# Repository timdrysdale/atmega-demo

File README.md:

# atmega-demo
PCB to demonstrate atmega microcontroller together with ACS712 and temperature sensor.

## Purpose

This board will be used to monitor power consumption and temperature in remote lab boxes.

## Schematic

The key components are an Atmega328P, a CH340 USB transceiver, an ACS712 current sensor and a simple analog temperature sensor. DTR reset is enabled to support re-programming over USB, while ICSP header is supplied for initial programming. Both CH340 and Atmega are using 12MHz crystals, which yields 0.1% baud rate error at 57600 baud for the Atmega.

## BOM

|Comment             |Designator         |Footprint                                                 |LCSC    |
|--------------------|-------------------|----------------------------------------------------------|--------|
|0.1n                |C1                 |Capacitor_SMD:C_0603_1608Metric                           |C100040 |
|100n                |C8,C11,C12         |Capacitor_SMD:C_0603_1608Metric                           |C14663  |
|0.1u                |C2,C3              |Capacitor_SMD:C_0603_1608Metric                           |C14663  |
|100n                |C4                 |Capacitor_SMD:C_0805_2012Metric                           |C49678  |
|22p                 |C5,C6              |Capacitor_SMD:C_0603_1608Metric                           |C1653   |
|4n7                 |C7                 |Capacitor_SMD:C_0603_1608Metric                           |C53987  |
|33p                 |C9,C10             |Capacitor_SMD:C_0603_1608Metric                           |C1663   |
|Green               |D1                 |LED_SMD:LED_0603_1608Metric                               |C72043  |
|Blue                |D2                 |LED_SMD:LED_0603_1608Metric                               |C72043  |
|PRTR5V0U2X          |D3                 |Package_TO_SOT_SMD:SOT-143                                |C2827688|
|Conn_01x04_Male     |J1                 |Connector_PinSocket_2.54mm:PinSocket_1x04_P2.54mm_Vertical|        |
|AVR_ICSP            |J2                 |Connector_PinHeader_2.54mm:PinHeader_2x03_P2.54mm_Vertical|        |
|USB_B_Micro         |J3                 |Connector_USB:USB_Micro-B_Amphenol_10118194_Horizontal    |C132563 |
|Screw_Terminal_01x02|J4                 |TerminalBlock:TerminalBlock_bornier-2_P5.08mm             |        |
|10u                 |L1                 |Inductor_SMD:L_0805_2012Metric                            |C1046   |
|10K                 |R1                 |Resistor_SMD:R_0603_1608Metric                            |C25804  |
|68                  |R2,R3              |Resistor_SMD:R_0603_1608Metric                            |C27592  |
|1M                  |R4                 |Resistor_SMD:R_0603_1608Metric                            |C22935  |
|NO                  |SW1                |Button_Switch_SMD:SW_SPST_PTS810                          |C116501 |
|TestPoint           |TP1,TP2,TP3,TP4,TP5|TestPoint:TestPoint_Keystone_5015_Micro-Minature          |C238130 |
|ACS712xLCTR-20A     |U1                 |Package_SO:SOIC-8_3.9x4.9mm_P1.27mm                       |C10681  |
|MCP9700T-HTT        |U2                 |Package_TO_SOT_SMD:SOT-23                                 |C150830 |
|ATmega328P-AU       |U3                 |Package_QFP:TQFP-32_7x7mm_P0.8mm                          |C14877  |
|CH340G              |U4                 |Package_SO:SOIC-16_3.9x9.9mm_P1.27mm                      |C14267  |
|12MHz               |Y1,Y2              |Crystal:Crystal_SMD_3225-4Pin_3.2x2.5mm                   |C97242  |

## Production

### DFM

The design for manufacture showed a couple of small issues:

The parts placement as shown on upload (known to disply with incorrect rotations):

The corrected placement after processing by JLCPCB (parts now oriented the same as the 3D output from KiCAD:

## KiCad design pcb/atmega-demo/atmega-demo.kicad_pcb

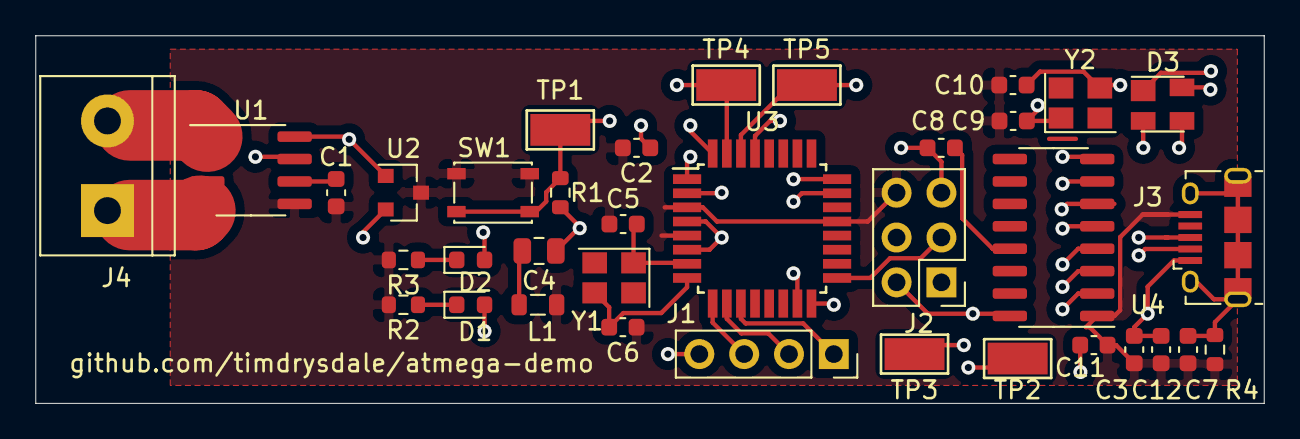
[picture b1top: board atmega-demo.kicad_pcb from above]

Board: 4 copper layers, 69.6 x 20.8 mm, 36 parts (0 on the bottom side), 31 nets.

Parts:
C1: 0.1n; C_0603_1608Metric
C2, C3: 0.1u; C_0603_1608Metric
C4: 100n; C_0805_2012Metric
C5, C6: 22p; C_0603_1608Metric
C7: 4n7; C_0603_1608Metric
C8, C11, C12: 100n; C_0603_1608Metric
C9, C10: 33p; C_0603_1608Metric
D1: Green; LED_0603_1608Metric
D2: Blue; LED_0603_1608Metric
D3: PRTR5V0U2X; SOT-143
J1: Conn_01x04_Male; PinSocket_1x04_P2.54mm_Vertical
J2: AVR_ICSP; PinHeader_2x03_P2.54mm_Vertical
J3: USB_B_Micro; USB_Micro-B_Amphenol_10118194_Horizontal
J4: Screw_Terminal_01x02; TerminalBlock_bornier-2_P5.08mm
L1: 10u; L_0805_2012Metric
R1: 10K; R_0603_1608Metric
R2, R3: 68; R_0603_1608Metric
R4: 1M; R_0603_1608Metric
SW1: NO; SW_SPST_PTS810
TP1, TP2, TP3, TP4, TP5: TestPoint; TestPoint_Keystone_5015_Micro-Minature
U1: ACS712xLCTR-20A; SOIC-8_3.9x4.9mm_P1.27mm
U2: MCP9700T-HTT; SOT-23
U3: ATmega328P-AU; TQFP-32_7x7mm_P0.8mm
U4: CH340G; SOIC-16_3.9x9.9mm_P1.27mm
Y1, Y2: 12MHz; Crystal_SMD_3225-4Pin_3.2x2.5mm

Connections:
+5V: C2.1, C3.1, C4.1, C12.1, D3.4, J2.2, J3.1, R1.1, U1.8, U2.1, U3.4, U3.6, U4.16
ADC: U1.7, U3.23
GND: C1.1, C2.2, C3.2, C5.1, C6.1, C7.1, C9.2, C10.2, C11.2, C12.2, J2.6, J3.5, L1.2, R2.2, R3.2, R4.1, SW1.2, U1.5, U2.3, U3.3, U3.5, U3.21, U4.1
unnamed: C1.2, U1.6
unnamed: C4.2, L1.1
unnamed: C5.2, U3.7, Y1.1
unnamed: C6.2, U3.8, Y1.3
unnamed: C7.2, D3.1, J3.6, R4.2
unnamed: C8.1, U4.13
unnamed: C8.2, J2.5, R1.2, SW1.1, TP1.1, U3.29
unnamed: C9.1, U4.7, Y2.1
unnamed: C10.1, U4.8, Y2.3
unnamed: C11.1, U4.4
unnamed: D1.1, R2.1
unnamed: D1.2, U3.1
unnamed: D2.1, R3.1
unnamed: D2.2, U3.32
unnamed: D3.2, J3.2, TP2.1, U4.6
unnamed: D3.3, J3.3, TP3.1, U4.5
unnamed: J1.1, U3.11
unnamed: J1.2, U3.10
unnamed: J1.3, U3.9
unnamed: J1.4, U3.2
unnamed: J2.1, U3.16
unnamed: J2.3, U3.17
unnamed: J2.4, U3.15
unnamed: J4.1, U1.3, U1.4
unnamed: J4.2, U1.1, U1.2
RXD: TP5.1, U3.30, U4.3
TEMP: U2.2, U3.24
TXD: TP4.1, U3.31, U4.2

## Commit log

2021-11-22 Initial design commit with 0805 and 3.6MHz osc
2021-11-23 Design as ordered
2021-11-23 Add DFM
